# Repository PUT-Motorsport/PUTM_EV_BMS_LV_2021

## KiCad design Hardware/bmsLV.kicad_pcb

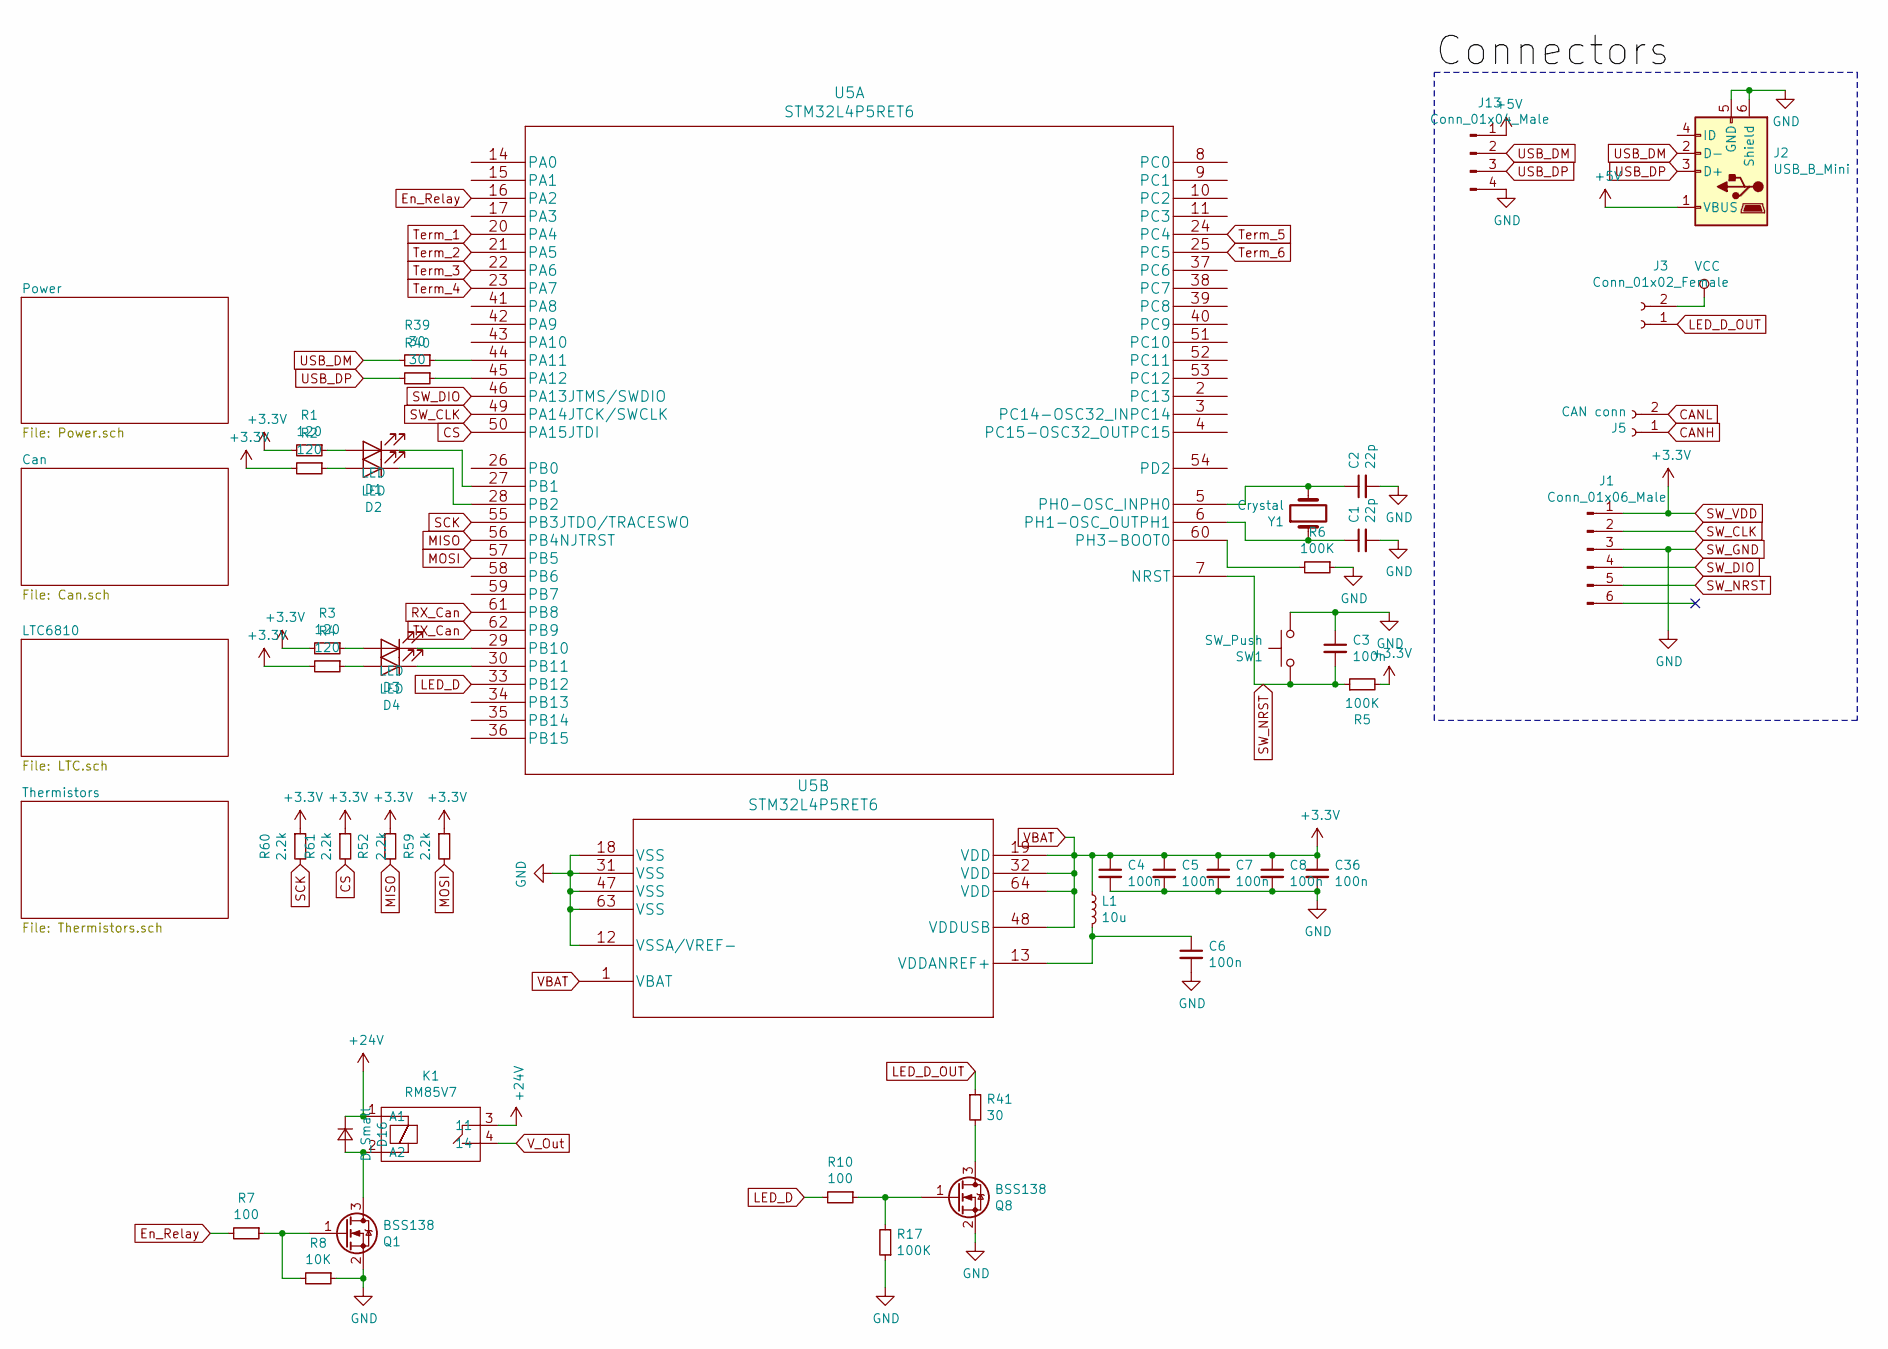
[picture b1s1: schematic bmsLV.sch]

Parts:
C1, C2: 22p; C_1206_3216Metric
C3, C4, C5, C6, C7, C8, C36: 100n; C_1206_3216Metric
D1, D2, D3, D4: LED; LED_1206_3216Metric
D16: D_Small; D_SMB
J1: Conn_01x06_Male; PinHeader_1x06_P2.54mm_Vertical
J2: USB_B_Mini; USB_Micro-B_Molex_47346-0001
J3: Conn_01x02_Female; PhoenixContact_MSTBVA_2,5_2-G-5,08_1x02_P5.08mm_Vertical
J5: CAN conn; PhoenixContact_MSTBVA_2,5_2-G-5,08_1x02_P5.08mm_Vertical
J13: Conn_01x04_Male; PinHeader_1x04_P2.54mm_Vertical
K1: RM85V7
L1: 10u; L_0805_2012Metric
Q1, Q8: BSS138; SOT-23
R1, R2, R3, R4: 120; R_1206_3216Metric
R5, R6, R17: 100K; R_1206_3216Metric
R7, R10: 100; R_1206_3216Metric
R8: 10K; R_1206_3216Metric
R39, R40, R41: 30; R_1206_3216Metric
R52, R59, R60, R61: 2.2k; R_1206_3216Metric
SW1: SW_Push; SW_PUSH_6mm
U5: STM32L4P5RET6
Y1: Crystal; Crystal_SMD_HC49-SD

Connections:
+5V: J2.1 (VBUS), J13.1; also elsewhere on the board
+24V: D16.1 (K), K1.1 (A1), K1.3 (11); also elsewhere on the board
CANH: J5.1; also elsewhere on the board
CANL: J5.2; also elsewhere on the board
CS: R61.2, U5.50 (PA15JTDI); also elsewhere on the board
En_Relay: R7.2, U5.16 (PA2)
LED_D: R10.2, U5.33 (PB12)
LED_D_OUT: J3.1, R41.1
MISO: R52.2, U5.56 (PB4NJTRST); also elsewhere on the board
MOSI: R59.2, U5.57 (PB5); also elsewhere on the board
unnamed: C1.1, U5.6 (PH1-OSC_OUTPH1), Y1.1
unnamed: C2.1, U5.5 (PH0-OSC_INPH0), Y1.2
unnamed: C6.1, L1.2, U5.13 (VDDANREF+)
unnamed: D1.1 (K), U5.27 (PB1)
unnamed: D1.2 (A), R1.1
unnamed: D2.1 (K), U5.28 (PB2)
unnamed: D2.2 (A), R2.1
unnamed: D3.1 (K), U5.29 (PB10)
unnamed: D3.2 (A), R3.1
unnamed: D4.1 (K), U5.30 (PB11)
unnamed: D4.2 (A), R4.1
unnamed: D16.2 (A), K1.2 (A2), Q1.3 (D)
unnamed: Q1.1 (G), R7.1, R8.2
unnamed: Q8.1 (G), R10.1, R17.2
unnamed: Q8.3 (D), R41.2
unnamed: R6.2, U5.60 (PH3-BOOT0)
unnamed: R39.1, U5.44 (PA11)
unnamed: R40.1, U5.45 (PA12)
RX_Can: U5.61 (PB8); also elsewhere on the board
SCK: R60.2, U5.55 (PB3JTDO/TRACESWO); also elsewhere on the board
SW_CLK: J1.2, U5.49 (PA14JTCK/SWCLK)
SW_DIO: J1.4, U5.46 (PA13JTMS/SWDIO)
SW_GND: C1.2, C2.2, C3.1, C4.2, C5.2, C6.2, C7.2, C8.2, C36.2, J1.3, J2.5 (GND), J2.6 (Shield), J13.4, Q1.2 (S), Q8.2 (S), R6.1, R8.1, R17.1, SW1.2, U5.12 (VSSA/VREF-), U5.18 (VSS), U5.31 (VSS), U5.47 (VSS), U5.63 (VSS); also elsewhere on the board
SW_NRST: C3.2, J1.5, R5.1, SW1.1, U5.7 (NRST)
SW_VDD: C4.1, C5.1, C7.1, C8.1, C36.1, J1.1, L1.1, R1.2, R2.2, R3.2, R4.2, R5.2, R52.1, R59.1, R60.1, R61.1, U5.1 (VBAT), U5.19 (VDD), U5.32 (VDD), U5.48 (VDDUSB), U5.64 (VDD); also elsewhere on the board
TX_Can: U5.62 (PB9); also elsewhere on the board
Term_1: U5.20 (PA4); also elsewhere on the board
Term_2: U5.21 (PA5); also elsewhere on the board
Term_3: U5.22 (PA6); also elsewhere on the board
Term_4: U5.23 (PA7); also elsewhere on the board
Term_5: U5.24 (PC4); also elsewhere on the board
Term_6: U5.25 (PC5); also elsewhere on the board
USB_DM: J2.2 (D-), J13.2, R39.2
USB_DP: J2.3 (D+), J13.3, R40.2
VCC: J3.2; also elsewhere on the board
V_Out: K1.4 (14)

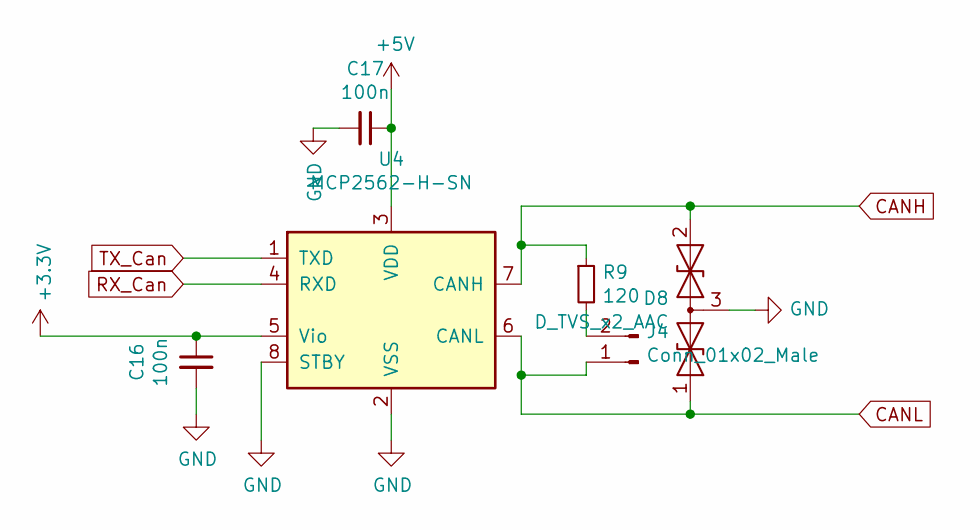
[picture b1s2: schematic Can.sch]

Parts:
C16, C17: 100n; C_1206_3216Metric
D8: D_TVS_x2_AAC; SOT-23
J4: Conn_01x02_Male; PinHeader_1x02_P2.54mm_Vertical
R9: 120; R_1206_3216Metric
U4: MCP2562-H-SN; SOIC-8_3.9x4.9mm_P1.27mm

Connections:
+5V: C17.1, U4.3 (VDD); also elsewhere on the board
CANH: D8.2 (A2), R9.1, U4.7 (CANH); also elsewhere on the board
CANL: D8.1 (A1), J4.1, U4.6 (CANL); also elsewhere on the board
unnamed: J4.2, R9.2
RX_Can: U4.4 (RXD); also elsewhere on the board
SW_GND: C16.2, C17.2, D8.3 (common), U4.2 (VSS), U4.8 (STBY); also elsewhere on the board
SW_VDD: C16.1, U4.5 (Vio); also elsewhere on the board
TX_Can: U4.1 (TXD); also elsewhere on the board

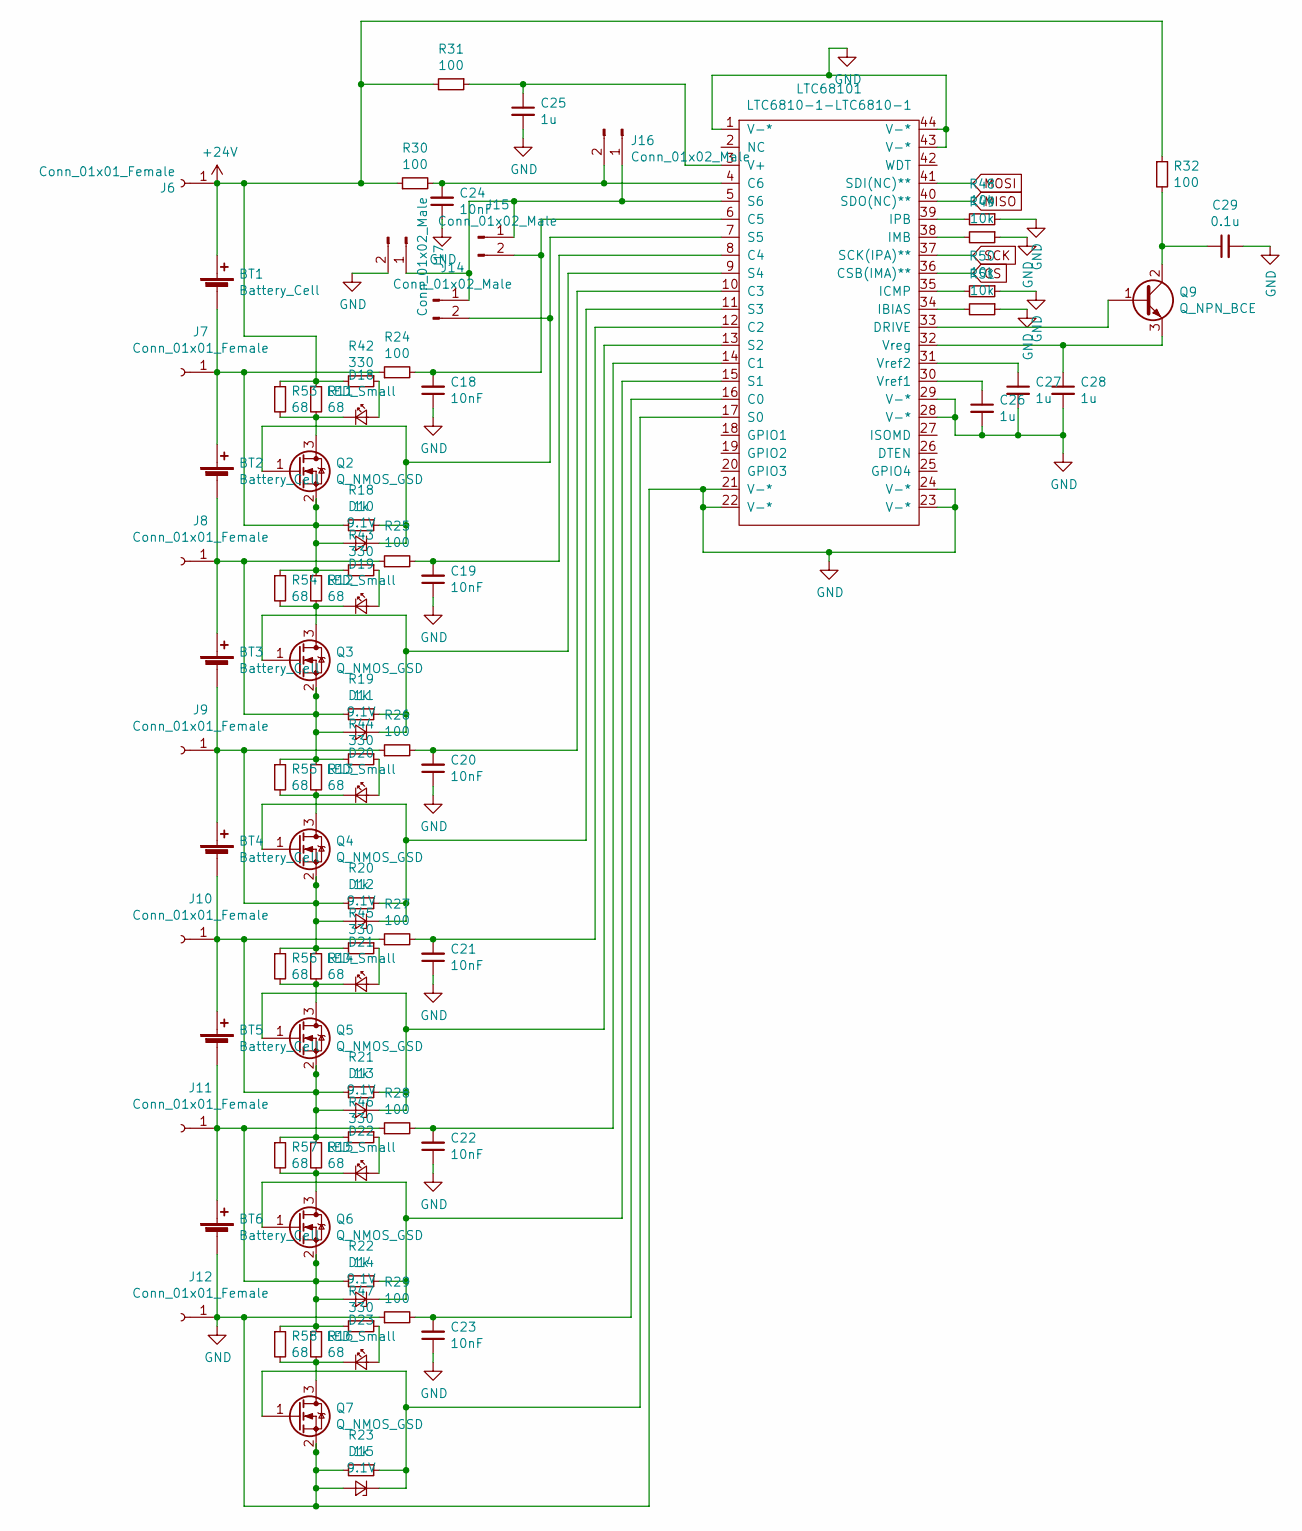
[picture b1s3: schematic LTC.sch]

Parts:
BT1, BT2, BT3, BT4, BT5, BT6: Battery_Cell; TerminalBlock_bornier-2_P5.08mm
C18, C19, C20, C21, C22, C23, C24: 10nF; C_1206_3216Metric
C25, C26, C27, C28: 1u; C_1206_3216Metric
C29: 0.1u; C_0603_1608Metric
D10, D11, D12, D13, D14, D15: 9.1V; D_SMB
D18, D19, D20, D21, D22, D23: LED_Small; LED_0805_2012Metric
J6, J7, J8, J9, J10, J11, J12: Conn_01x01_Female; CellPad
J14, J15, J16, J17: Conn_01x02_Male; SolderJumper-2_P1.3mm_Open_RoundedPad1.0x1.5mm
LTC68101: LTC6810-1-LTC6810-1; LTC6810
Q2, Q3, Q4, Q5, Q6, Q7: Q_NMOS_GSD; SOT-23
Q9: Q_NPN_BCE; SOT-23W
R11, R12, R13, R14, R15, R16, R53, R54, R55, R56, R57, R58: 68; R_2512_6332Metric
R18, R19, R20, R21, R22, R23: 1k; R_1206_3216Metric
R24, R25, R26, R27, R28, R29, R30, R31, R32: 100; R_1206_3216Metric
R42, R43, R44, R45, R46, R47: 330; R_1206_3216Metric
R48, R49, R50, R51: 10k; R_0805_2012Metric

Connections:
+24V: BT1.1 (+), J6.1, R11.1, R30.1, R31.2, R32.1, R42.2, R53.1; also elsewhere on the board
CS: LTC68101.36 (CSB(IMA)**); also elsewhere on the board
MISO: LTC68101.40 (SDO(NC)**); also elsewhere on the board
MOSI: LTC68101.41 (SDI(NC)**); also elsewhere on the board
unnamed: BT1.2 (-), BT2.1 (+), D10.2 (A), J7.1, Q2.2 (S), R12.1, R18.2, R24.1, R43.2, R54.1
unnamed: BT2.2 (-), BT3.1 (+), D11.2 (A), J8.1, Q3.2 (S), R13.1, R19.2, R25.1, R44.2, R55.1
unnamed: BT3.2 (-), BT4.1 (+), D12.2 (A), J9.1, Q4.2 (S), R14.1, R20.2, R26.1, R45.2, R56.1
unnamed: BT4.2 (-), BT5.1 (+), D13.2 (A), J10.1, Q5.2 (S), R15.1, R21.2, R27.1, R46.2, R57.1
unnamed: BT5.2 (-), BT6.1 (+), D14.2 (A), J11.1, Q6.2 (S), R16.1, R22.2, R28.1, R47.2, R58.1
unnamed: C18.2, J15.2, LTC68101.6 (C5), R24.2
unnamed: C19.2, LTC68101.8 (C4), R25.2
unnamed: C20.2, LTC68101.10 (C3), R26.2
unnamed: C21.2, LTC68101.12 (C2), R27.2
unnamed: C22.2, LTC68101.14 (C1), R28.2
unnamed: C23.2, LTC68101.16 (C0), R29.2
unnamed: C24.2, J16.2, LTC68101.4 (C6), R30.2
unnamed: C25.1, LTC68101.3 (V+), R31.1
unnamed: C26.1, LTC68101.30 (Vref1)
unnamed: C27.1, LTC68101.31 (Vref2)
unnamed: C28.1, LTC68101.32 (Vreg), Q9.3 (E)
unnamed: C29.1, Q9.2 (C), R32.2
unnamed: D10.1 (K), J14.2, LTC68101.7 (S5), Q2.1 (G), R18.1
unnamed: D11.1 (K), LTC68101.9 (S4), Q3.1 (G), R19.1
unnamed: D12.1 (K), LTC68101.11 (S3), Q4.1 (G), R20.1
unnamed: D13.1 (K), LTC68101.13 (S2), Q5.1 (G), R21.1
unnamed: D14.1 (K), LTC68101.15 (S1), Q6.1 (G), R22.1
unnamed: D15.1 (K), LTC68101.17 (S0), Q7.1 (G), R23.1
unnamed: D18.1 (K), Q2.3 (D), R11.2, R53.2
unnamed: D18.2 (A), R42.1
unnamed: D19.1 (K), Q3.3 (D), R12.2, R54.2
unnamed: D19.2 (A), R43.1
unnamed: D20.1 (K), Q4.3 (D), R13.2, R55.2
unnamed: D20.2 (A), R44.1
unnamed: D21.1 (K), Q5.3 (D), R14.2, R56.2
unnamed: D21.2 (A), R45.1
unnamed: D22.1 (K), Q6.3 (D), R15.2, R57.2
unnamed: D22.2 (A), R46.1
unnamed: D23.1 (K), Q7.3 (D), R16.2, R58.2
unnamed: D23.2 (A), R47.1
unnamed: J14.1, J15.1, J16.1, J17.1, LTC68101.5 (S6)
unnamed: LTC68101.33 (DRIVE), Q9.1 (B)
unnamed: LTC68101.34 (IBIAS), R51.2
unnamed: LTC68101.35 (ICMP), R50.2
unnamed: LTC68101.38 (IMB), R49.2
unnamed: LTC68101.39 (IPB), R48.2
SCK: LTC68101.37 (SCK(IPA)**); also elsewhere on the board
SW_GND: BT6.2 (-), C18.1, C19.1, C20.1, C21.1, C22.1, C23.1, C24.1, C25.2, C26.2, C27.2, C28.2, C29.2, D15.2 (A), J12.1, J17.2, LTC68101.1 (V-*), LTC68101.21 (V-*), LTC68101.22 (V-*), LTC68101.23 (V-*), LTC68101.24 (V-*), LTC68101.28 (V-*), LTC68101.29 (V-*), LTC68101.43 (V-*), LTC68101.44 (V-*), Q7.2 (S), R23.2, R29.1, R48.1, R49.1, R50.1, R51.1; also elsewhere on the board

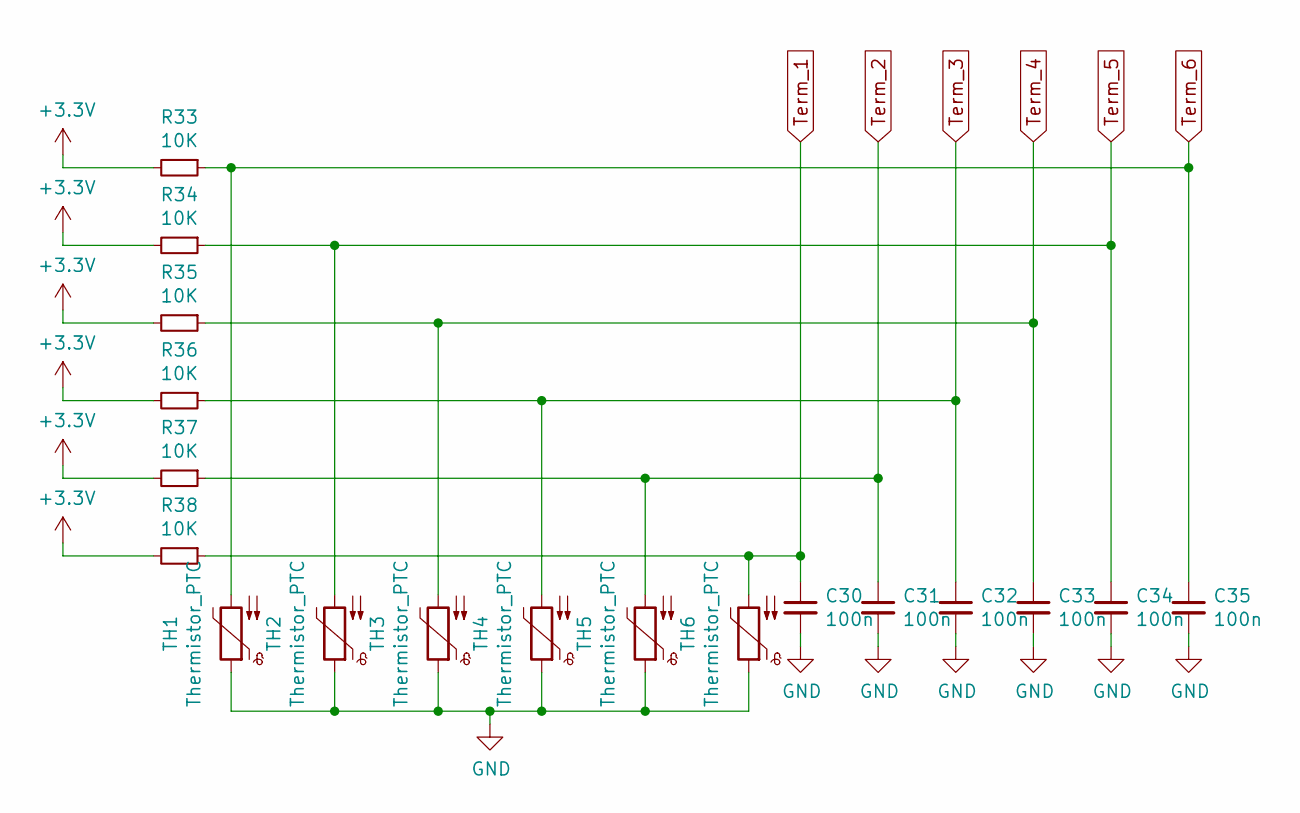
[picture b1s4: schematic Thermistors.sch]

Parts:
C30, C31, C32, C33, C34, C35: 100n; C_1206_3216Metric
R33, R34, R35, R36, R37, R38: 10K; R_1206_3216Metric
TH1, TH2, TH3, TH4, TH5, TH6: Thermistor_PTC; PinHeader_1x02_P2.54mm_Vertical

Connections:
SW_GND: C30.2, C31.2, C32.2, C33.2, C34.2, C35.2, TH1.1, TH2.1, TH3.1, TH4.1, TH5.1, TH6.1; also elsewhere on the board
SW_VDD: R33.2, R34.2, R35.2, R36.2, R37.2, R38.2; also elsewhere on the board
Term_1: C30.1, R38.1, TH6.2; also elsewhere on the board
Term_2: C31.1, R37.1, TH5.2; also elsewhere on the board
Term_3: C32.1, R36.1, TH4.2; also elsewhere on the board
Term_4: C33.1, R35.1, TH3.2; also elsewhere on the board
Term_5: C34.1, R34.1, TH2.2; also elsewhere on the board
Term_6: C35.1, R33.1, TH1.2; also elsewhere on the board

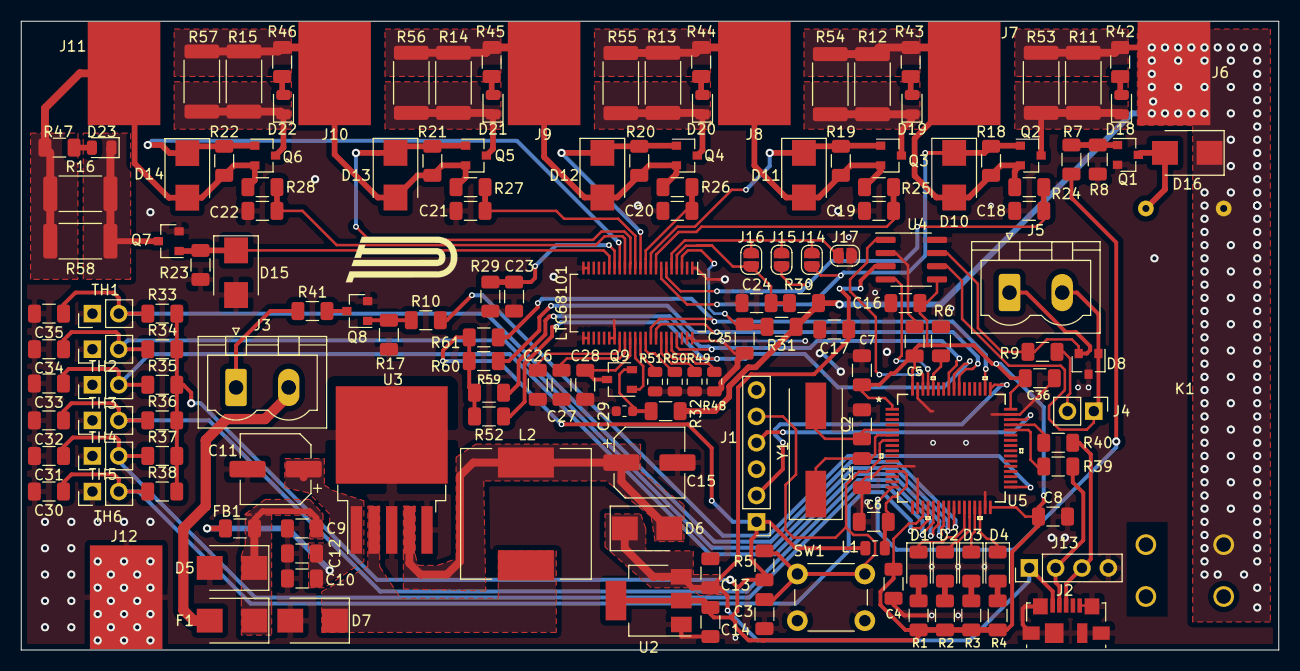
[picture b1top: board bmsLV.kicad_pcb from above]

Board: 2 copper layers, 121.2 x 60.6 mm, 162 parts (0 on the bottom side), 91 nets.

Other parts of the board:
C9: 330p; C_1206_3216Metric
C10: 47n; C_1206_3216Metric
C11: 680u; CP_Elec_6.3x7.7
C12, C13, C14: 100n; C_1206_3216Metric
C15: 220uF; CP_Elec_6.3x7.7
D5, D6, D7: D_Schottky; D_SMB
F1: Fuse; D_SMB
FB1: Ferrite_Bead_Small; C_1206_3216Metric
L2: 33u; L_12x12mm_H8mm
U2: LM1117-3.3; SOT-223-3_TabPin2
U3: LM2596S-5; TO-263-5_TabPin3

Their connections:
+5V: C13.1, D6.1, U2.3; also elsewhere on the board
+5VD: C15.1, D6.2, L2.2, U3.4
unnamed: C9.1, D5.1, F1.1, FB1.2
unnamed: C10.1, C11.1, C12.1, FB1.1, U3.1
unnamed: D7.1, L2.1, U3.2
SW_GND: C9.2, C10.2, C11.2, C12.2, C13.2, C14.2, C15.2, D5.2, D7.2, U2.1, U3.3, U3.5; also elsewhere on the board
SW_VDD: C14.1, U2.2; also elsewhere on the board
VCC: F1.2; also elsewhere on the board

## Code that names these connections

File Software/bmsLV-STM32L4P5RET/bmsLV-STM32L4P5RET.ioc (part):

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Mcu.Name=STM32L4P5R(G-E)Tx
Mcu.Package=LQFP64
Mcu.UserName=STM32L4P5RETx
PA11.Mode=Device_Only
PA11.Signal=USB_OTG_FS_DM
PA12.Mode=Device_Only
PA12.Signal=USB_OTG_FS_DP
PA13\ (JTMS/SWDIO).GPIOParameters=GPIO_Label
PA13\ (JTMS/SWDIO).GPIO_Label=SW_DIO
PA13\ (JTMS/SWDIO).Mode=Serial_Wire
PA13\ (JTMS/SWDIO).Signal=SYS_JTMS-SWDIO
PA14\ (JTCK/SWCLK).GPIOParameters=GPIO_Label
PA14\ (JTCK/SWCLK).GPIO_Label=SW_CLK
PA14\ (JTCK/SWCLK).Mode=Serial_Wire
PA14\ (JTCK/SWCLK).Signal=SYS_JTCK-SWCLK
PA15\ (JTDI).GPIOParameters=GPIO_Speed,PinState,GPIO_Label
PA15\ (JTDI).GPIO_Label=SPI1_CS
PA15\ (JTDI).GPIO_Speed=GPIO_SPEED_FREQ_HIGH
PA15\ (JTDI).PinState=GPIO_PIN_RESET
PA15\ (JTDI).Signal=GPIO_Output
PA2.GPIOParameters=PinState,GPIO_Label,GPIO_ModeDefaultOutputPP
PA2.GPIO_Label=RELAY
PA2.GPIO_ModeDefaultOutputPP=GPIO_MODE_OUTPUT_PP
PA2.PinState=GPIO_PIN_RESET
PA2.Signal=GPIO_Output
PA4.GPIOParameters=GPIO_Label
PA4.GPIO_Label=TERM_1
PA4.Signal=ADCx_IN9
PA5.GPIOParameters=GPIO_Label
PA5.GPIO_Label=TERM_2
PA5.Signal=ADCx_IN10
PA6.GPIOParameters=GPIO_Label
PA6.GPIO_Label=TERM_3
PA6.Signal=ADCx_IN11
PA7.GPIOParameters=GPIO_Label
PA7.GPIO_Label=TERM_4
PA7.Signal=ADCx_IN12
PB1.GPIOParameters=GPIO_Label
PB1.GPIO_Label=SENSOR
PB1.Signal=ADCx_IN16
PB10.GPIOParameters=PinState,GPIO_Label,GPIO_ModeDefaultOutputPP
PB10.GPIO_Label=LED_3
PB10.GPIO_ModeDefaultOutputPP=GPIO_MODE_OUTPUT_PP
PB10.PinState=GPIO_PIN_SET
PB10.Signal=GPIO_Output
PB11.GPIOParameters=PinState,GPIO_Label,GPIO_ModeDefaultOutputPP
PB11.GPIO_Label=LED_4
PB11.GPIO_ModeDefaultOutputPP=GPIO_MODE_OUTPUT_PP
PB11.PinState=GPIO_PIN_SET
PB11.Signal=GPIO_Output
PB12.GPIOParameters=GPIO_Label,GPIO_ModeDefaultOutputPP
PB12.GPIO_Label=LED_DASH
PB12.GPIO_ModeDefaultOutputPP=GPIO_MODE_OUTPUT_PP
PB12.Signal=GPIO_Output
PB2.GPIOParameters=PinState,GPIO_Label,GPIO_ModeDefaultOutputPP
PB2.GPIO_Label=LED_2
PB2.GPIO_ModeDefaultOutputPP=GPIO_MODE_OUTPUT_PP
PB2.PinState=GPIO_PIN_SET
PB2.Signal=GPIO_Output
PB3\ (JTDO/TRACESWO).Mode=Full_Duplex_Master
PB3\ (JTDO/TRACESWO).Signal=SPI1_SCK
PB4\ (NJTRST).GPIOParameters=GPIO_PuPd
PB4\ (NJTRST).GPIO_PuPd=GPIO_PULLUP
PB4\ (NJTRST).Mode=Full_Duplex_Master
PB4\ (NJTRST).Signal=SPI1_MISO
PB5.Mode=Full_Duplex_Master
PB5.Signal=SPI1_MOSI
PB8.Mode=CAN_Activate
PB8.Signal=CAN1_RX
PB9.Mode=CAN_Activate
PB9.Signal=CAN1_TX
PC4.GPIOParameters=GPIO_Label
PC4.GPIO_Label=TERM_5
PC4.Signal=ADCx_IN13
PC5.GPIOParameters=GPIO_Label
PC5.GPIO_Label=TERM_6
PC5.Signal=ADCx_IN14
PH0-OSC_IN\ (PH0).Mode=HSE-External-Oscillator
PH0-OSC_IN\ (PH0).Signal=RCC_OSC_IN
PH1-OSC_OUT\ (PH1).Mode=HSE-External-Oscillator
PH1-OSC_OUT\ (PH1).Signal=RCC_OSC_OUT
RCC.HSE_VALUE=16000000
RCC.SYSCLKFreq_VALUE=64000000
RCC.SYSCLKSource=RCC_SYSCLKSOURCE_PLLCLK
board=custom

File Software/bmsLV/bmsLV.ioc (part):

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Mcu.Name=STM32F103C(8-B)Tx
Mcu.Package=LQFP48
Mcu.UserName=STM32F103C8Tx
PA11.Mode=Device
PA11.Signal=USB_DM
PA12.Mode=Device
PA12.Signal=USB_DP
PA13.Mode=Serial_Wire
PA13.Signal=SYS_JTMS-SWDIO
PA14.Mode=Serial_Wire
PA14.Signal=SYS_JTCK-SWCLK
PA15.Mode=NSS_Signal_Hard_Output
PA15.Signal=SPI1_NSS
PA2.GPIOParameters=GPIO_Label
PA2.GPIO_Label=RELAY
PA2.Signal=GPIO_Output
PA3.GPIOParameters=GPIO_Label
PA3.GPIO_Label=TERM_1
PA3.Signal=ADCx_IN3
PA4.GPIOParameters=GPIO_Label
PA4.GPIO_Label=TERM_2
PA4.Signal=ADCx_IN4
PA5.GPIOParameters=GPIO_Label
PA5.GPIO_Label=TERM_3
PA5.Signal=ADCx_IN5
PA6.GPIOParameters=GPIO_Label
PA6.GPIO_Label=TERM_4
PA6.Signal=ADCx_IN6
PA7.GPIOParameters=GPIO_Label
PA7.GPIO_Label=TERM_5
PA7.Signal=ADCx_IN7
PB0.GPIOParameters=GPIO_Label
PB0.GPIO_Label=TERM_6
PB0.Signal=ADCx_IN8
PB1.GPIOParameters=GPIO_Label
PB1.GPIO_Label=LED_1
PB1.Signal=GPIO_Output
PB10.GPIOParameters=GPIO_Label
PB10.GPIO_Label=LED_3
PB10.Signal=GPIO_Output
PB11.GPIOParameters=GPIO_Label
PB11.GPIO_Label=LED_4
PB11.Signal=GPIO_Output
PB12.GPIOParameters=GPIO_Label
PB12.GPIO_Label=LED_D
PB12.Signal=GPIO_Output
PB2.GPIOParameters=GPIO_Label
PB2.GPIO_Label=LED_2
PB2.Signal=GPIO_Output
PB3.Mode=Full_Duplex_Master
PB3.Signal=SPI1_SCK
PB4.Mode=Full_Duplex_Master
PB4.Signal=SPI1_MISO
PB5.Mode=Full_Duplex_Master
PB5.Signal=SPI1_MOSI
PB8.Mode=CAN_Activate
PB8.Signal=CAN_RX
PB9.Mode=CAN_Activate
PB9.Signal=CAN_TX
PD0-OSC_IN.Mode=HSE-External-Oscillator
PD0-OSC_IN.Signal=RCC_OSC_IN
PD1-OSC_OUT.Mode=HSE-External-Oscillator
PD1-OSC_OUT.Signal=RCC_OSC_OUT
RCC.HSE_VALUE=16000000
RCC.SYSCLKFreq_VALUE=48000000
RCC.SYSCLKSource=RCC_SYSCLKSOURCE_PLLCLK
board=custom

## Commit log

2021-01-09 Test
    Test
2021-01-09 Hardware init
    Scheme ready
2021-01-09 Deleted wrong files
2021-01-09 Cosmetic changes in files
2021-01-14 Power update
2021-02-14 Save before ZCO version
2021-02-15 ZCO version
2021-02-24 Save before ZCO version- back
2021-02-24 Save before ZCO version- back 2
2021-02-24 Save before ZCO version- back 3
2021-02-24 Going back to work
2021-02-25 pcb layout nearly done
2021-02-26 PCB layout v1
2021-03-04 PCB v2
    changes in scheme:
    NMOS->PMOS in LTC balance
    S6 LTC pinout deleted
    another discharge resistor added on every S# LTC pinout and value changed from 30 to 68 on both
    PCB changes:
    CAN position changed
2021-03-12 PCB finished
    PCB finished and ready to check
2021-04-12 PCB changes + MXCube
    -gitignore added to the Hardware and Software sections
    -Changed power section wiring on PCB
    -MXCube file created as a beginning of Software section
2021-04-13 J13, J14, J15 footprint change
2021-04-13 Dash Led and jumpers
    -output to Dash Led created
    -added another jumper (J17) to ground
    -J14, J15, J16 jumper position changed
2021-04-14 Repository cleaning
2021-04-19 Connector footrpint changed
2021-04-22 Relay 3D model
    Relay 3D model added to footprint.
    Footprint of that relay changed a little.
2021-04-29 STM changed
    Due to the lack of processors on market, we decided to change STM32F103C8T6 for STM32F4P5RET. So the schematic and PCB is significantly changed in this area.
    Furthermore, the library and footprint to new processor was added.
2021-04-29 Update pcb
    Small update of some elements signatures
2021-04-30 CS and CLK pull up added
2021-05-02 Checked By SS
2021-05-03 Some changes
2021-05-05 PUTM Logos added
2021-05-10 gitignore modified
2021-05-10 footprint update
2021-06-24 Software update (check description)
    -SPI connection with LTC
    -CAN functions (init and Tx)
    -measuring of all cell voltage
    -some balance functions (not ended tho)
    -check error function (need to test it)
    I didnt add any functions related to temperatures.
2021-07-01 Software update 2
    -ADC and temperatures functions added
    -Check error function rewrited and tested
    -Some changes in CAN massages
    Everythink works except cell balancing.
2021-08-05 Software update 3
    Current sensor added to PCB (through wires)
    Current sensor handling added
    Cell balance working! (HUGE PART OF UPDATE)
    CheckError function modified (a lot of more error added)
    Serial print function added (not tested)
    + some cosmetic changes
2021-08-06 Software update 4
    -Working serial print through USB
    -Code lifting (useless variables removed, some comments added and general code cleaning)
2021-08-06 balanceControl and some #defines changes
2021-08-22 State of Charge feature added
    State of Charge feature added
    + balance function changed in the last charging part
    + cosmetic changes
2021-09-19 Balance function changed
    Balance function changed in the last part of charging

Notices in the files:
parts and their libraries:
Copyright 2016 Accelerated Designs. All rights reserved.
